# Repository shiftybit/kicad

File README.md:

# Circuitry Projects
This is primarily a repository created for me to keep track of all my misc electronics project in one place. In here you will find kicad projects and libraries, misc arduino sketches, cherry tree notebooks (though these will be converted to markdown in the near future.

## Circuit Atlanta ToDo List
- [ ] Identify list of buildings to make.
- [ ] Use icarus board to identify addressable led strategy. 

## Circuit Atlanta Buildings
- [ ] AT&T Building (partially complete)
	- [x] SVG Reference
	- [x] Logo
	- [x] Windows
	- [ ] Scale, Size, and Dimensions
		- In order to scale, I need to have other buildings available. 
- [ ] Westin
	- [ ] Westin Logo
	- [ ] Need to do something about the bottom ring of lights
	- [ ] Something to do with the sundial restaurant. 
- [ ] Bank of America Building
	- I'm curious about how to do the top here.
	- Current plan is to do naked FR4 material and use basic LEDS mounted behind the FR4 to diffuse the orange/yellowish light through the substrate material. 
		- I could investigate other substrate materials here to achieve a different effect. 
- [ ] SunTrust Plaza
	- This building is my favorite building in atlanta, and I think I will have the most fun with this.
	- It seems relatively simple. 
- [ ] Georgia Pacific Building
	- Also seems pretty easy.
- [ ] Equitable building
	- Super simple building. Plus big identifable logo. Win Win

This leaves me a total of 6 buildings for a skyline. I feel like I need at least 9 to make the skyline easily identifiable. I want somebody seeing this peice of art to immediately know this is atlanta. It needs to be iconic and recognizable.

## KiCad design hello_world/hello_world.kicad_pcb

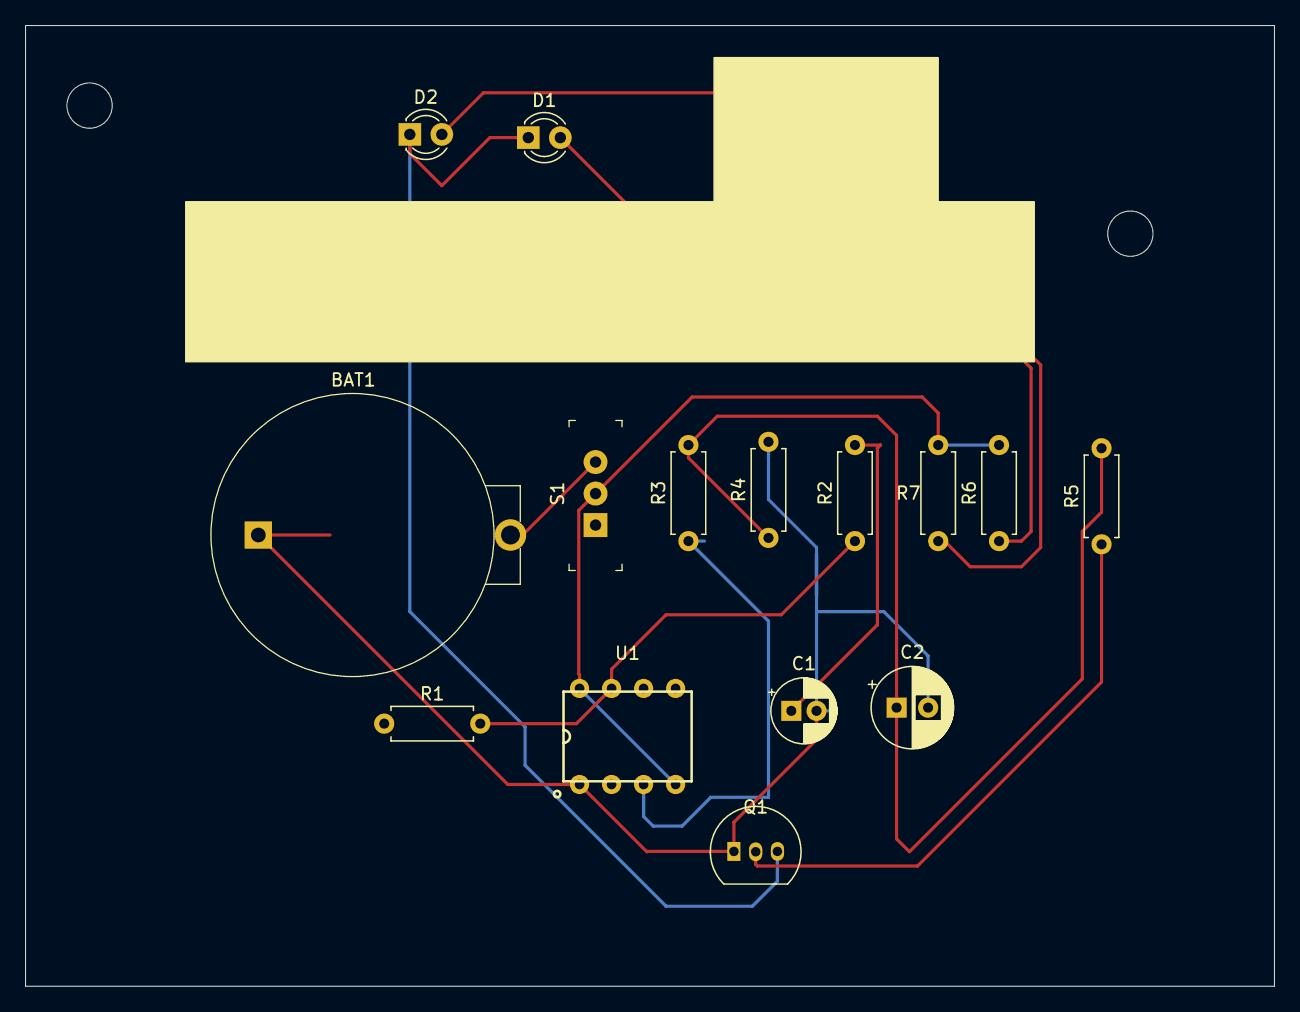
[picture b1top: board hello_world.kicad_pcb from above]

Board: 2 copper layers, 99.1 x 76.2 mm, 15 parts (0 on the bottom side), 11 nets.

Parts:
BAT1: BS-7; Battery_Holder_Coin_2032_BS-7
C1: 10uF; CP_Radial_D5.0mm_P2.00mm
C2: 100uF; CP_Radial_D6.3mm_P2.50mm
D1, D2: RED; LED_D3.0mm
Q1: 2N3904; TO-92_Inline_fixed
R1, R3: 22k; R_Axial_DIN0207_L6.3mm_D2.5mm_P7.62mm_Horizontal
R2: 330k; R_Axial_DIN0207_L6.3mm_D2.5mm_P7.62mm_Horizontal
R4: 100k; R_Axial_DIN0207_L6.3mm_D2.5mm_P7.62mm_Horizontal
R5: 10k; R_Axial_DIN0207_L6.3mm_D2.5mm_P7.62mm_Horizontal
R6, R7: 100; R_Axial_DIN0207_L6.3mm_D2.5mm_P7.62mm_Horizontal
S1: EG1218; Switch_Slide_11.6x4mm_EG1218
U1: 7555; ICM7555-PDIP

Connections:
GND: BAT1.Neg, C1.2, C2.2, Q1.1, R4.2, U1.1
unnamed: BAT1.Pos, S1.3
unnamed: C1.1, R2.2
unnamed: C2.1, R3.2, R4.1, R5.2
unnamed: D1.1, D2.1, Q1.3
unnamed: D1.2, R6.1
unnamed: D2.2, R7.1
unnamed: Q1.2, R5.1
unnamed: R1.2, R2.1, U1.7
unnamed: R3.1, U1.3
VCC: R6.2, R7.2, S1.2, U1.4, U1.8

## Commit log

2019-08-22 Kicad
2019-08-24 added notes
2019-08-26 tweaking kitt rendering
2019-08-27 added hello world
2019-08-29 fixed TO-92 Inline for 2N3904 Transistor. Added additional 1mm spacing between pads. Adjusted footprint silkscreen and fab layers to make it bigger.
2019-09-03 major finishes to kittByHand
2019-09-03 I guess this is a checkin
2019-09-21 First BOM
2019-09-22 added stuff
2019-09-22 Added Top Logo
2019-09-23 top_logo_test
2019-09-26 Finished Kitt FootPrint
2019-10-02 skyline
2019-10-02 added docs
2019-10-02 att_building_outline
2019-10-02 att draft 1 finished
2019-10-02 working at&t building
2019-10-05 stuff i did at bnb
2019-10-05 i found a westin hotel clipart!
2019-10-13 file updates
2019-10-13 .gitignore. Documentation for flipflop IC
2019-10-18 Led driver Research
2019-11-19 added icarus v2.0 this was needed for working with the ws2811 chips. needed a quick prototype board for working with that specific smd chip
2019-11-30 uncommitted changes. Not sure what they are.
2019-12-10 sizing adjustments
2019-12-14 corrected sunled pad numbers
2020-02-01 I believe this was added for me to test my individual ws8211 chip.
2020-02-01 Fixed Icarus. Actually routed the tracks for the ws2811 dip adapter
2020-02-01 Added Readme for the project
2020-02-02 Added westin windows
2020-02-05 Added RGB and GND fab layers to the Sunled PLCC4 thingy

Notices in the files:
hello_world/hello_world.kicad_pcb:
License: CC BY 4.0
